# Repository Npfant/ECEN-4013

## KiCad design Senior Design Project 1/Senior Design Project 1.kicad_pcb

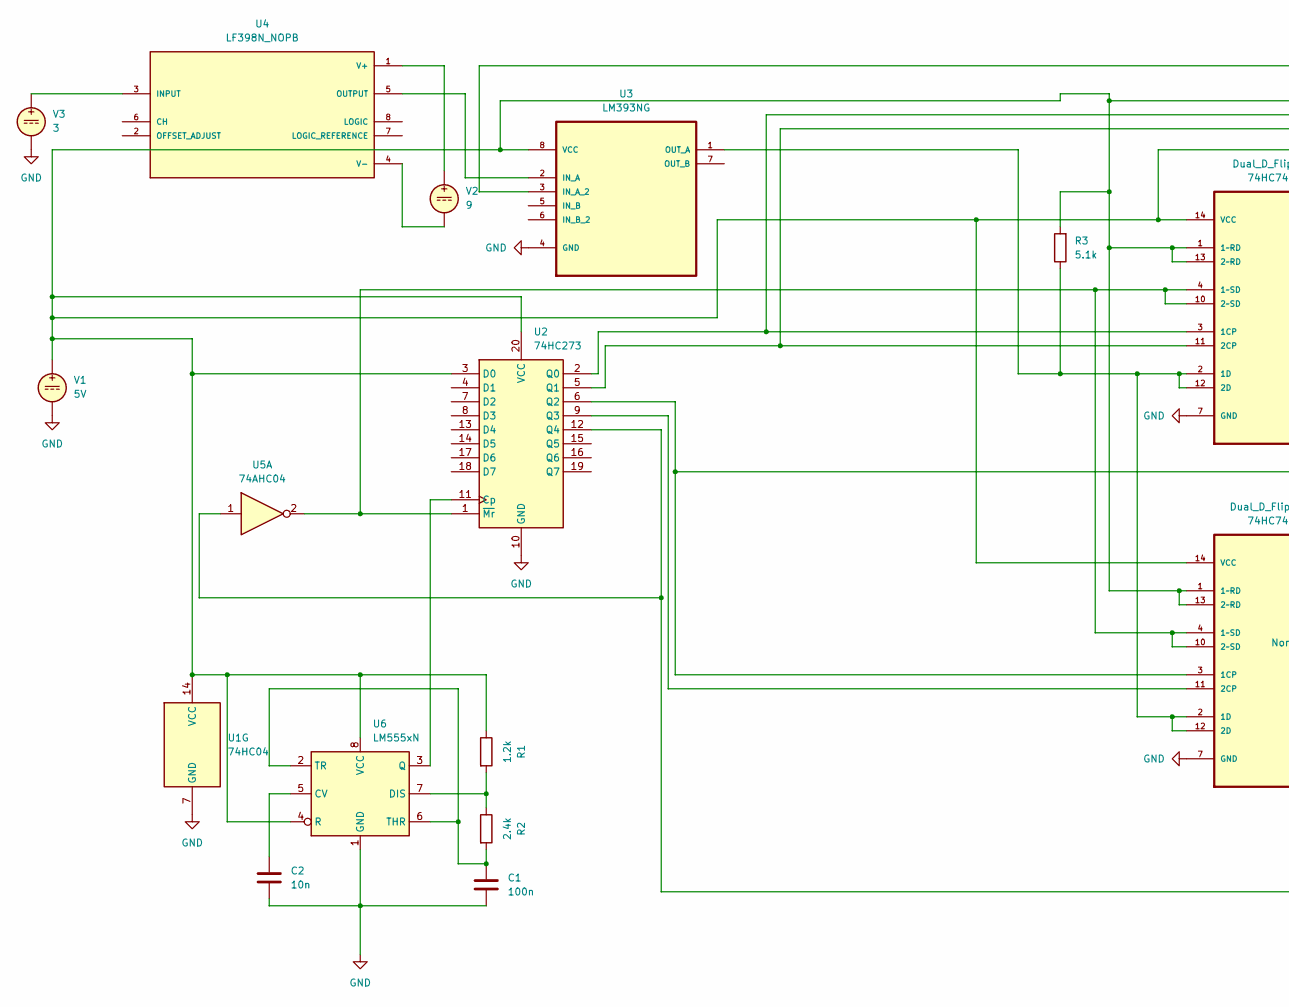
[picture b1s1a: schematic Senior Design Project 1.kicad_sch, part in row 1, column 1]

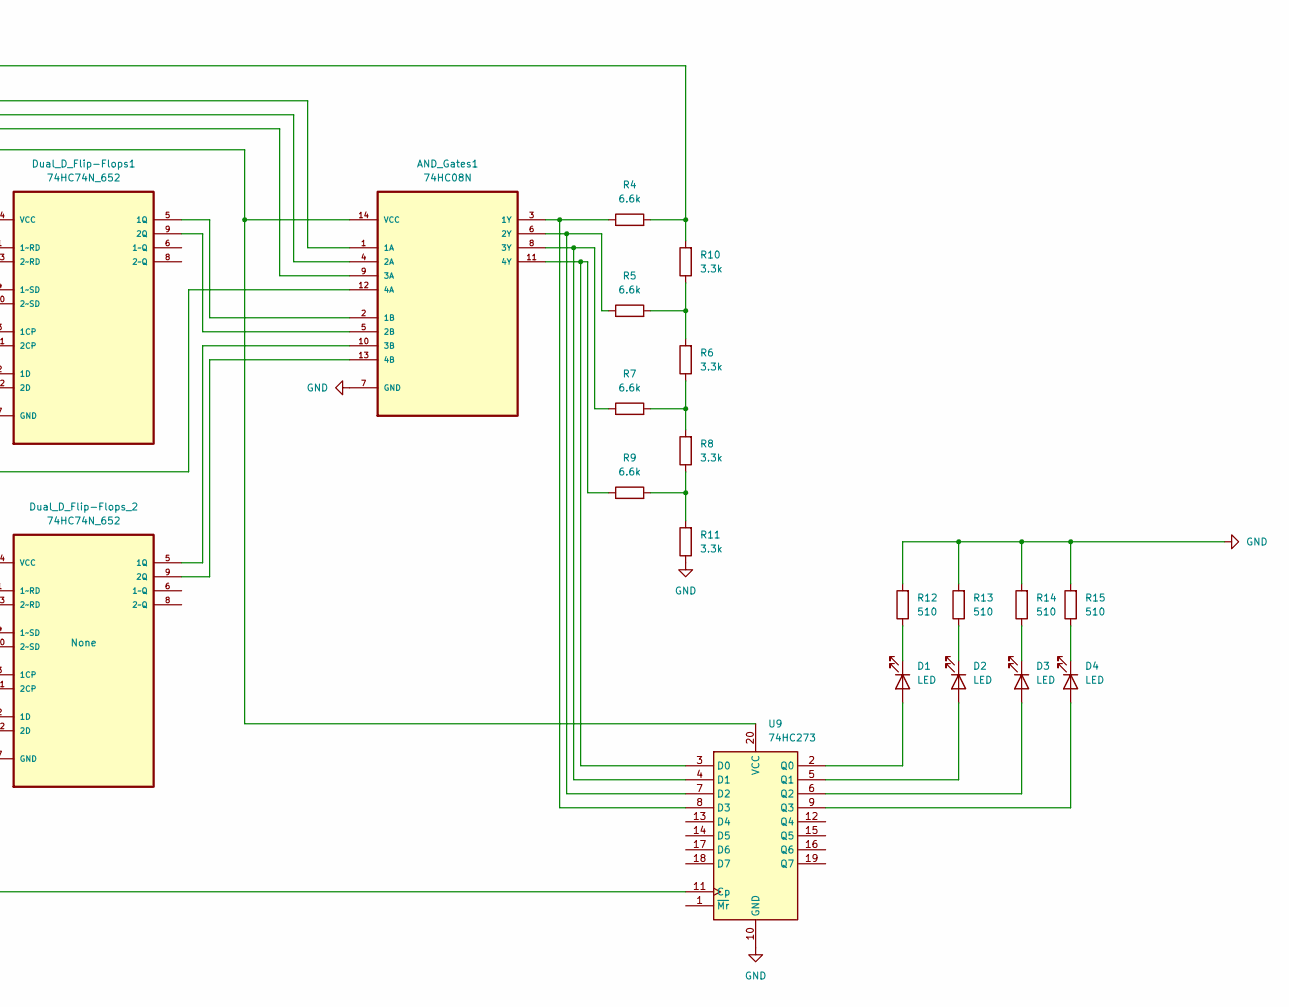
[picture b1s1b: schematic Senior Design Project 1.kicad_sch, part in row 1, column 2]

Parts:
AND_Gates1: 74HC08N; DIP254P762X420-14; MPN 74HC08N
C1: 100n; CP_Radial_D6.3mm_P2.50mm
C2: 10n; CP_Radial_D6.3mm_P2.50mm
D1, D2, D3, D4: LED; LED_D3.0mm_Horizontal_O6.35mm_Z10.0mm
Dual_D_Flip-Flops1: 74HC74N_652; DIP254P762X420-14; MPN 74HC74N,652
Dual_D_Flip-Flops_2: 74HC74N_652; DIP254P762X420-14; MPN 74HC74N,652
R1: 1.2k; R_Axial_DIN0204_L3.6mm_D1.6mm_P7.62mm_Horizontal
R2: 2.4k; R_Axial_DIN0204_L3.6mm_D1.6mm_P7.62mm_Horizontal
R3: 5.1k; R_Axial_DIN0204_L3.6mm_D1.6mm_P7.62mm_Horizontal
R4, R5, R7, R9: 6.6k; R_Axial_DIN0204_L3.6mm_D1.6mm_P7.62mm_Horizontal
R6, R8, R10, R11: 3.3k; R_Axial_DIN0204_L3.6mm_D1.6mm_P7.62mm_Horizontal
R12, R13, R14, R15: 510; R_Axial_DIN0204_L3.6mm_D1.6mm_P7.62mm_Horizontal
U1: 74HC04
U2, U9: 74HC273; DIP254P762X508-20
U3: LM393NG; DIP254P762X533-8; MPN LM393NG
U4: LF398N_NOPB; DIP794W45P254L959H508Q8; PARTREV C
U5: 74AHC04; DIP254P762X420-14
U6: LM555xN; DIP-8_W7.62mm
V1: 5V; TerminalBlock_bornier-3_P5.08mm
V2: 9; TerminalBlock_4Ucon_1x02_P3.50mm_Vertical
V3: 3; TerminalBlock_4Ucon_1x02_P3.50mm_Vertical

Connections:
GND: AND_Gates1.7 (GND), C1.2, C2.2, Dual_D_Flip-Flops1.7 (GND), Dual_D_Flip-Flops_2.7 (GND), R11.1, R12.2, R13.2, R14.2, R15.2, U1.7 (GND), U2.10 (GND), U3.4 (GND), U6.1 (GND), U9.10 (GND), V1.2, V3.2
unnamed: AND_Gates1.1 (1A), AND_Gates1.14 (VCC), Dual_D_Flip-Flops1.1 (1~RD), Dual_D_Flip-Flops1.13 (2~RD), Dual_D_Flip-Flops1.14 (VCC), Dual_D_Flip-Flops_2.1 (1~RD), Dual_D_Flip-Flops_2.13 (2~RD), Dual_D_Flip-Flops_2.14 (VCC), R1.1, R3.2, U1.14 (VCC), U2.3 (D0), U2.20 (VCC), U3.8 (VCC), U6.4 (R), U6.8 (VCC), U9.20 (VCC), V1.1
unnamed: AND_Gates1.2 (1B), Dual_D_Flip-Flops1.5 (1Q)
unnamed: AND_Gates1.3 (1Y), R4.1, U9.8 (D3)
unnamed: AND_Gates1.4 (2A), Dual_D_Flip-Flops1.3 (1CP), U2.2 (Q0)
unnamed: AND_Gates1.5 (2B), Dual_D_Flip-Flops1.9 (2Q)
unnamed: AND_Gates1.6 (2Y), R5.1, U9.7 (D2)
unnamed: AND_Gates1.9 (3A), Dual_D_Flip-Flops1.11 (2CP), U2.5 (Q1)
unnamed: AND_Gates1.10 (3B), Dual_D_Flip-Flops_2.5 (1Q)
unnamed: AND_Gates1.8 (3Y), R7.1, U9.4 (D1)
unnamed: AND_Gates1.12 (4A), Dual_D_Flip-Flops_2.3 (1CP), U2.6 (Q2)
unnamed: AND_Gates1.13 (4B), Dual_D_Flip-Flops_2.9 (2Q)
unnamed: AND_Gates1.11 (4Y), R9.1, U9.3 (D0)
unnamed: D1.2 (A), U9.2 (Q0)
unnamed: D1.1 (K), R12.1
unnamed: D2.2 (A), U9.5 (Q1)
unnamed: D2.1 (K), R13.1
unnamed: D3.2 (A), U9.6 (Q2)
unnamed: D3.1 (K), R14.1
unnamed: D4.2 (A), U9.9 (Q3)
unnamed: D4.1 (K), R15.1
unnamed: Dual_D_Flip-Flops1.2 (1D), Dual_D_Flip-Flops1.12 (2D), Dual_D_Flip-Flops_2.2 (1D), Dual_D_Flip-Flops_2.12 (2D), R3.1, U3.1 (OUT_A)
unnamed: Dual_D_Flip-Flops1.4 (1~SD), Dual_D_Flip-Flops1.10 (2~SD), Dual_D_Flip-Flops_2.4 (1~SD), Dual_D_Flip-Flops_2.10 (2~SD), U2.1 (~Mr), U5.2
unnamed: Dual_D_Flip-Flops_2.11 (2CP), U2.9 (Q3)
unnamed: R6.1, R7.2, R8.2
unnamed: R5.2, R6.2, R10.1
unnamed: R8.1, R9.2, R11.2
unnamed: U2.11 (Cp), U6.3 (Q)
unnamed: U2.12 (Q4), U5.1, U9.11 (Cp)
unnamed: U3.2 (IN_A), U4.5 (OUTPUT)
unnamed: R4.2, R10.2, U3.3 (IN_A_2)
unnamed: U4.3 (INPUT), V3.1
unnamed: U4.1 (V+), V2.1
unnamed: U4.4 (V-), V2.2
unnamed: C2.1, U6.5 (CV)
unnamed: R1.2, R2.1, U6.7 (DIS)
unnamed: C1.1, R2.2, U6.2 (TR), U6.6 (THR)

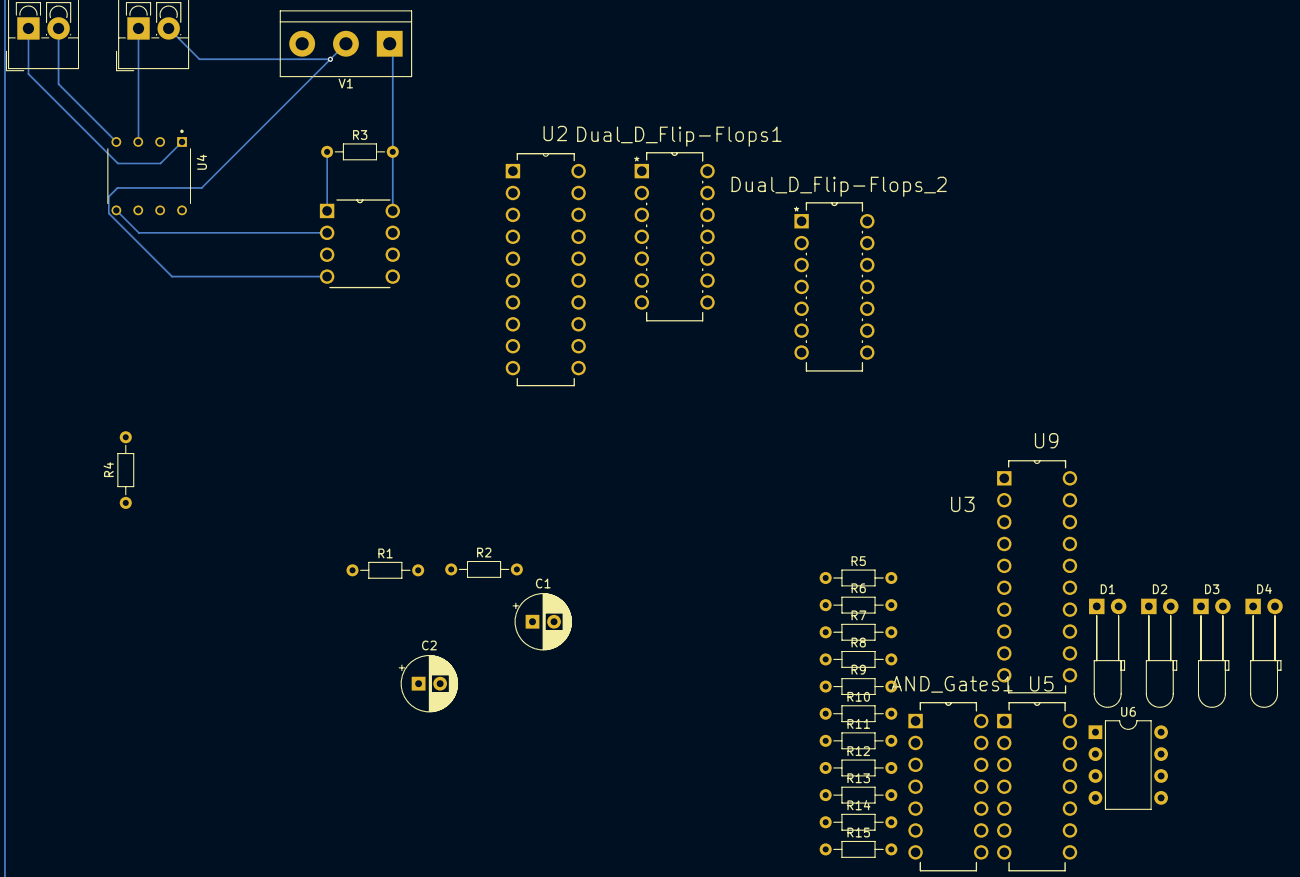
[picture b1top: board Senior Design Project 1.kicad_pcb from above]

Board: 2 copper layers, 33 parts (0 on the bottom side), 37 nets.

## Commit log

2024-09-10 INIT
    Added MultiSim files
2024-09-10 Added NE555 timer to simulation
    Runs at 1.25 kHz
2024-09-10 Cleaned up layout
2024-09-12 Converted to manual operation
2024-09-12 Updated resistor values
2024-09-20 Uploaded WIP PCB to Github
2024-09-23 Added components & footprints
2024-09-24 Modified initialization procedure
2024-09-25 Added Flip-Flop Footprint library
2024-09-25 Added more libraries
2024-09-25 Added library folders to github file
2024-09-25 Added Dual Flip-flop schematic & footprint
2024-09-25 Added comparator library
2024-09-28 Fixed digital signal error.
2024-09-29 Schematic Done for PCB Build
2024-09-29 PCB Board Created; Parts Placed
2024-09-29 Saves
2024-09-30 Updated Schematic & PCB
2024-10-05 Footprint fixes and updated PCB design
